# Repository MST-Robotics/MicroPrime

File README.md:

# MicroPrime
Repository for MicroPrime PR Robot

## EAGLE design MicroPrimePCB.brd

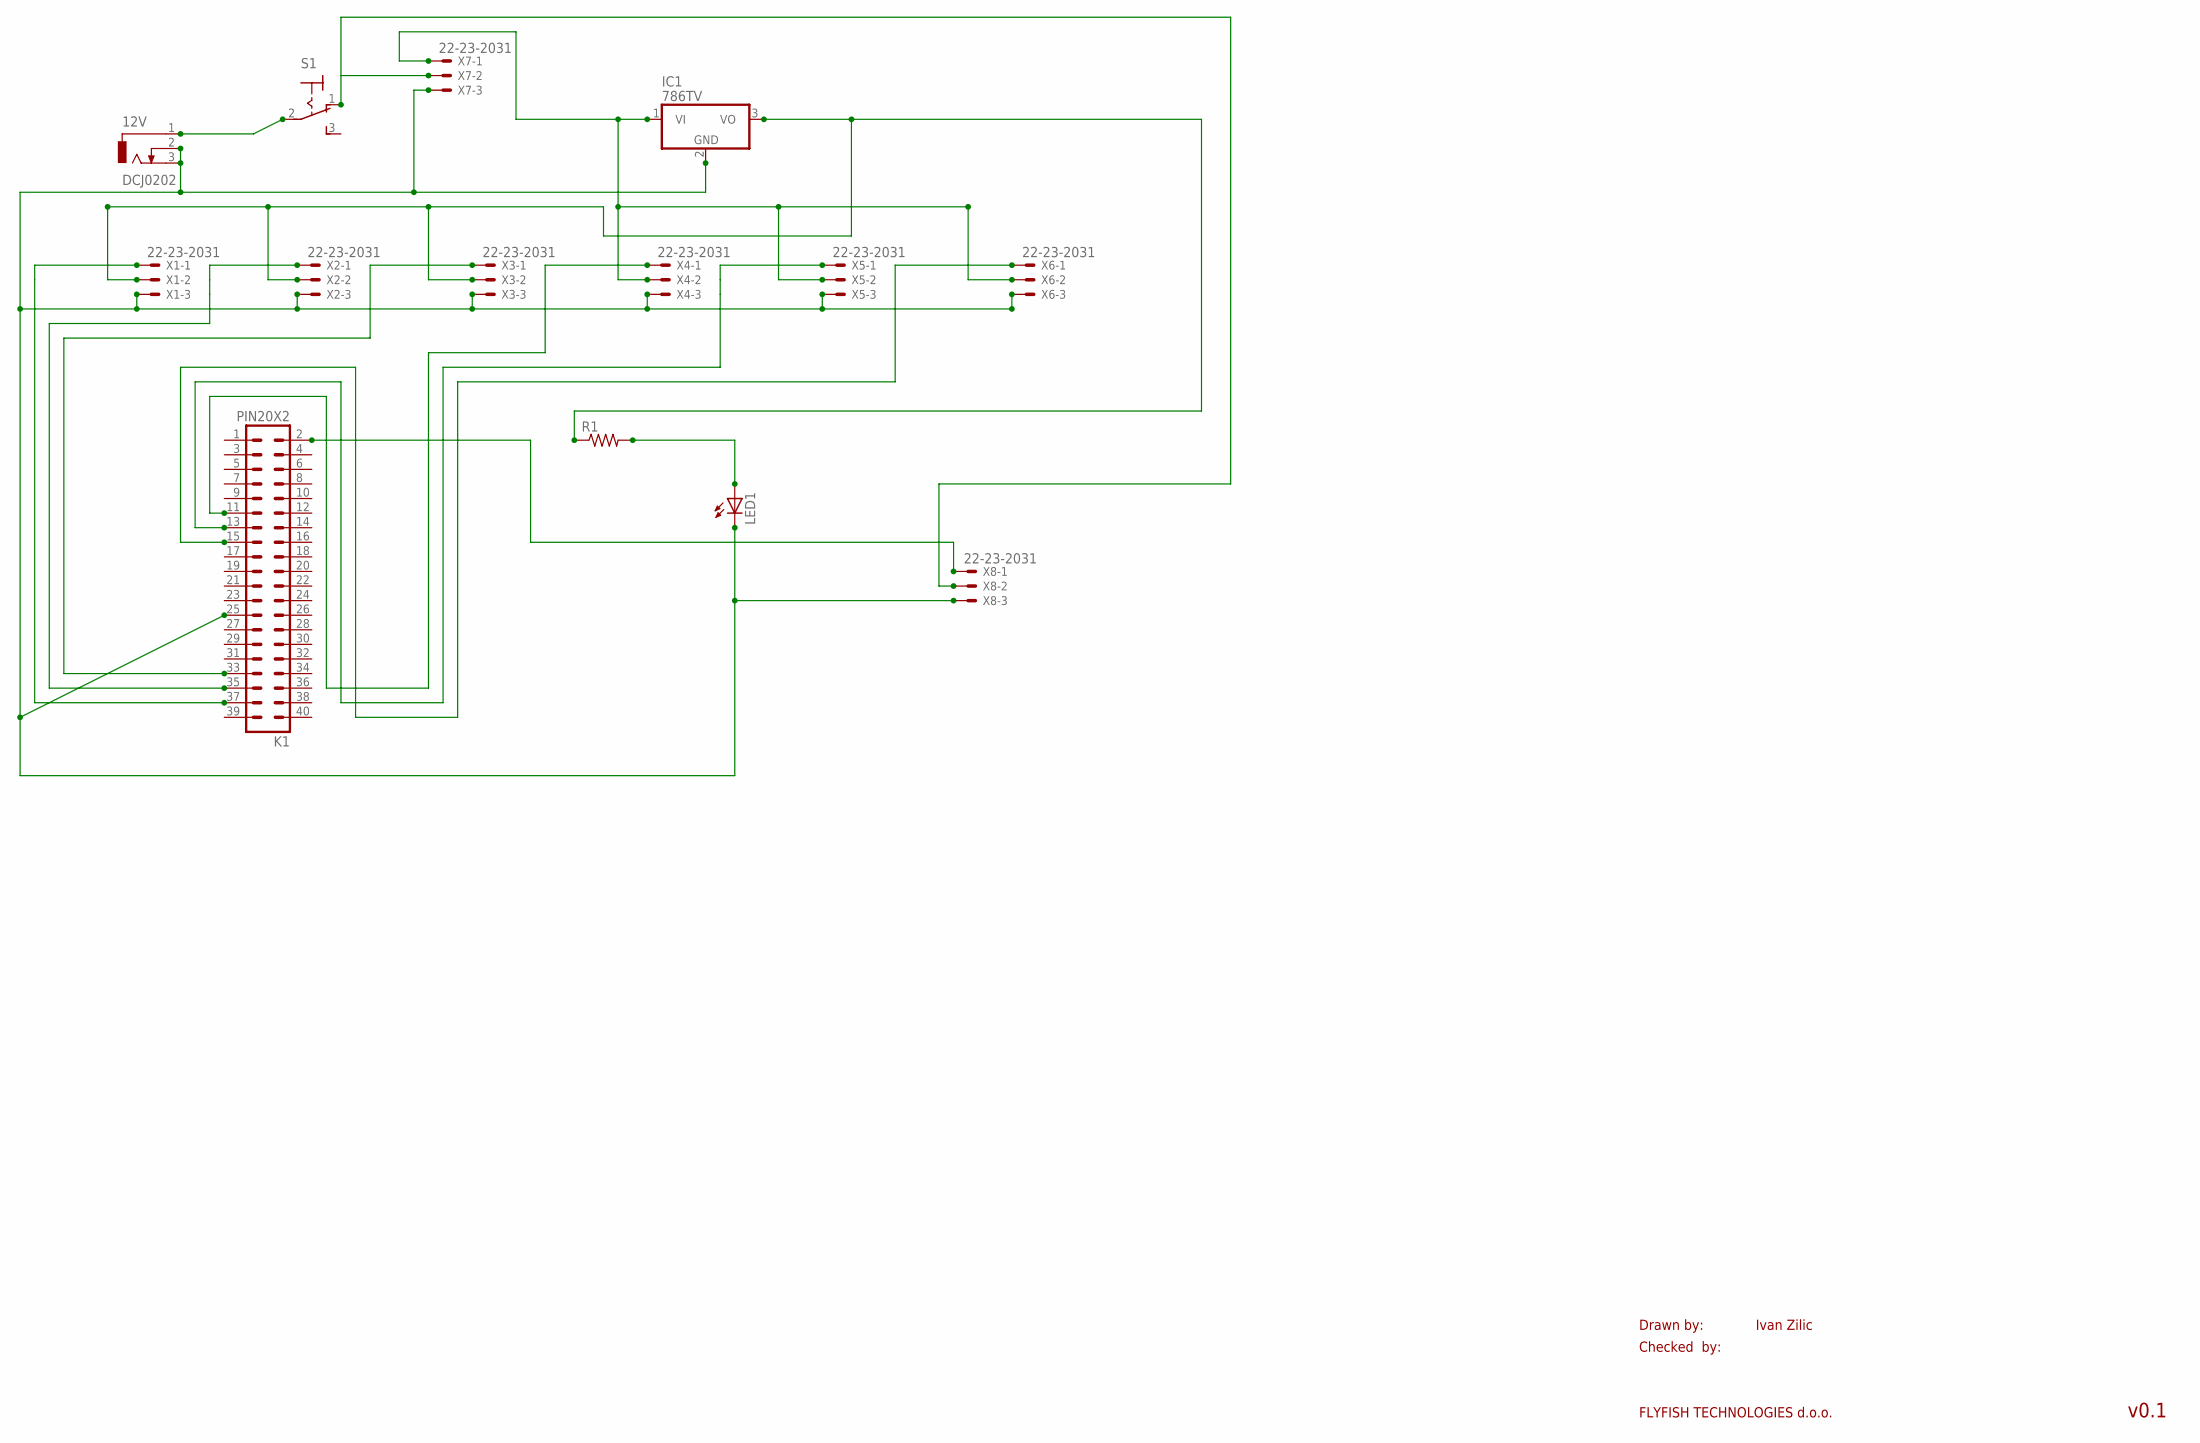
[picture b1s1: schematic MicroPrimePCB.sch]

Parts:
12V: DCJ0202
IC1: 786TV; TO220V
K1: PIN20X2; PIN_20X2
LED1: LED_ELD260; LED_LD260
R1: R-US_0204/7; 0204/7
S1: 320-916
X1, X2, X3, X4, X5, X6, X7, X8: 22-23-2031

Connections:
unnamed: 12V.1, S1.2
unnamed: IC1.1 (VI), X4.2, X5.2, X6.2, X7.1
unnamed: 12V.2, 12V.3, IC1.2 (GND), K1.25, LED1.K (C), X1.3, X2.3, X3.3, X4.3, X5.3, X6.3, X7.3, X8.3
unnamed: K1.2, X8.1
unnamed: S1.1 (O), X7.2, X8.2
unnamed: LED1.A, R1.2
unnamed: K1.37, X1.1
unnamed: K1.35, X2.1
unnamed: K1.33, X3.1
unnamed: IC1.3 (VO), R1.1, X1.2, X2.2, X3.2
unnamed: K1.11, X4.1
unnamed: K1.13, X5.1
unnamed: K1.15, X6.1

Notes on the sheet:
Drawn by:
Checked by:
FLYFISH TECHNOLOGIES d.o.o.
Ivan Zilic
v0.1

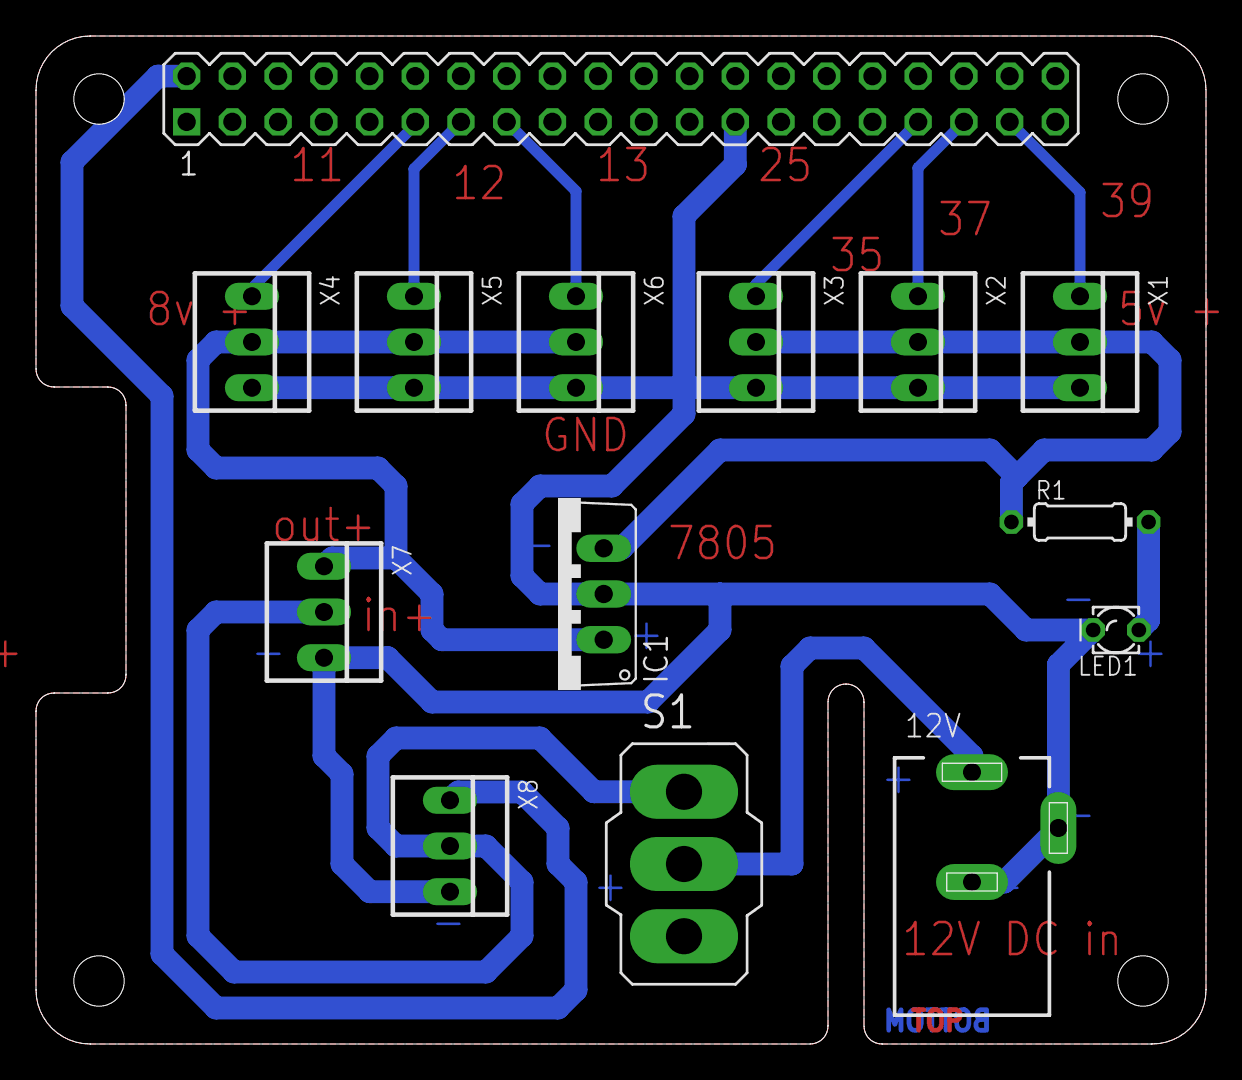
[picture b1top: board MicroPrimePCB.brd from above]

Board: 2 copper layers, 65.0 x 56.0 mm, 15 parts (0 on the bottom side), 13 nets.

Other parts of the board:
DRILEGEND: DRILEGEND

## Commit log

2015-01-30 Add Eagle CAD files for PCB
    This is a Schematic and Final PCB design for micro' Circuit's
2015-02-03 Add arduino code for MicroPrime
    Updated Arduino Code that will allow eah servo to be indipendantly controlled by the xbox controller
2015-02-03 Add a folder for Arduino code
2015-02-05 Remove old files
    Cleaned up old files, to be replaced by updated versions in next commit
2015-02-05 Clean code with proper formating
    CLeaned up code, now has code to print to the serial monitor the relevent values, and has been commented properly.
2015-02-05 Add code to scale servos properly
    Put Code to Scale Servos into a function, and 'Prettied' the code up a bit
2015-02-06 Add code to make MicroPrime work
    Code Now works as desired on an arduino, The function could still afford to be optimized though]
2015-02-26 Add variable speed control
    Added a speed control to the continuous rotation servo, scaled at 1/20 the speed
2015-02-26 Add folder for schematics
